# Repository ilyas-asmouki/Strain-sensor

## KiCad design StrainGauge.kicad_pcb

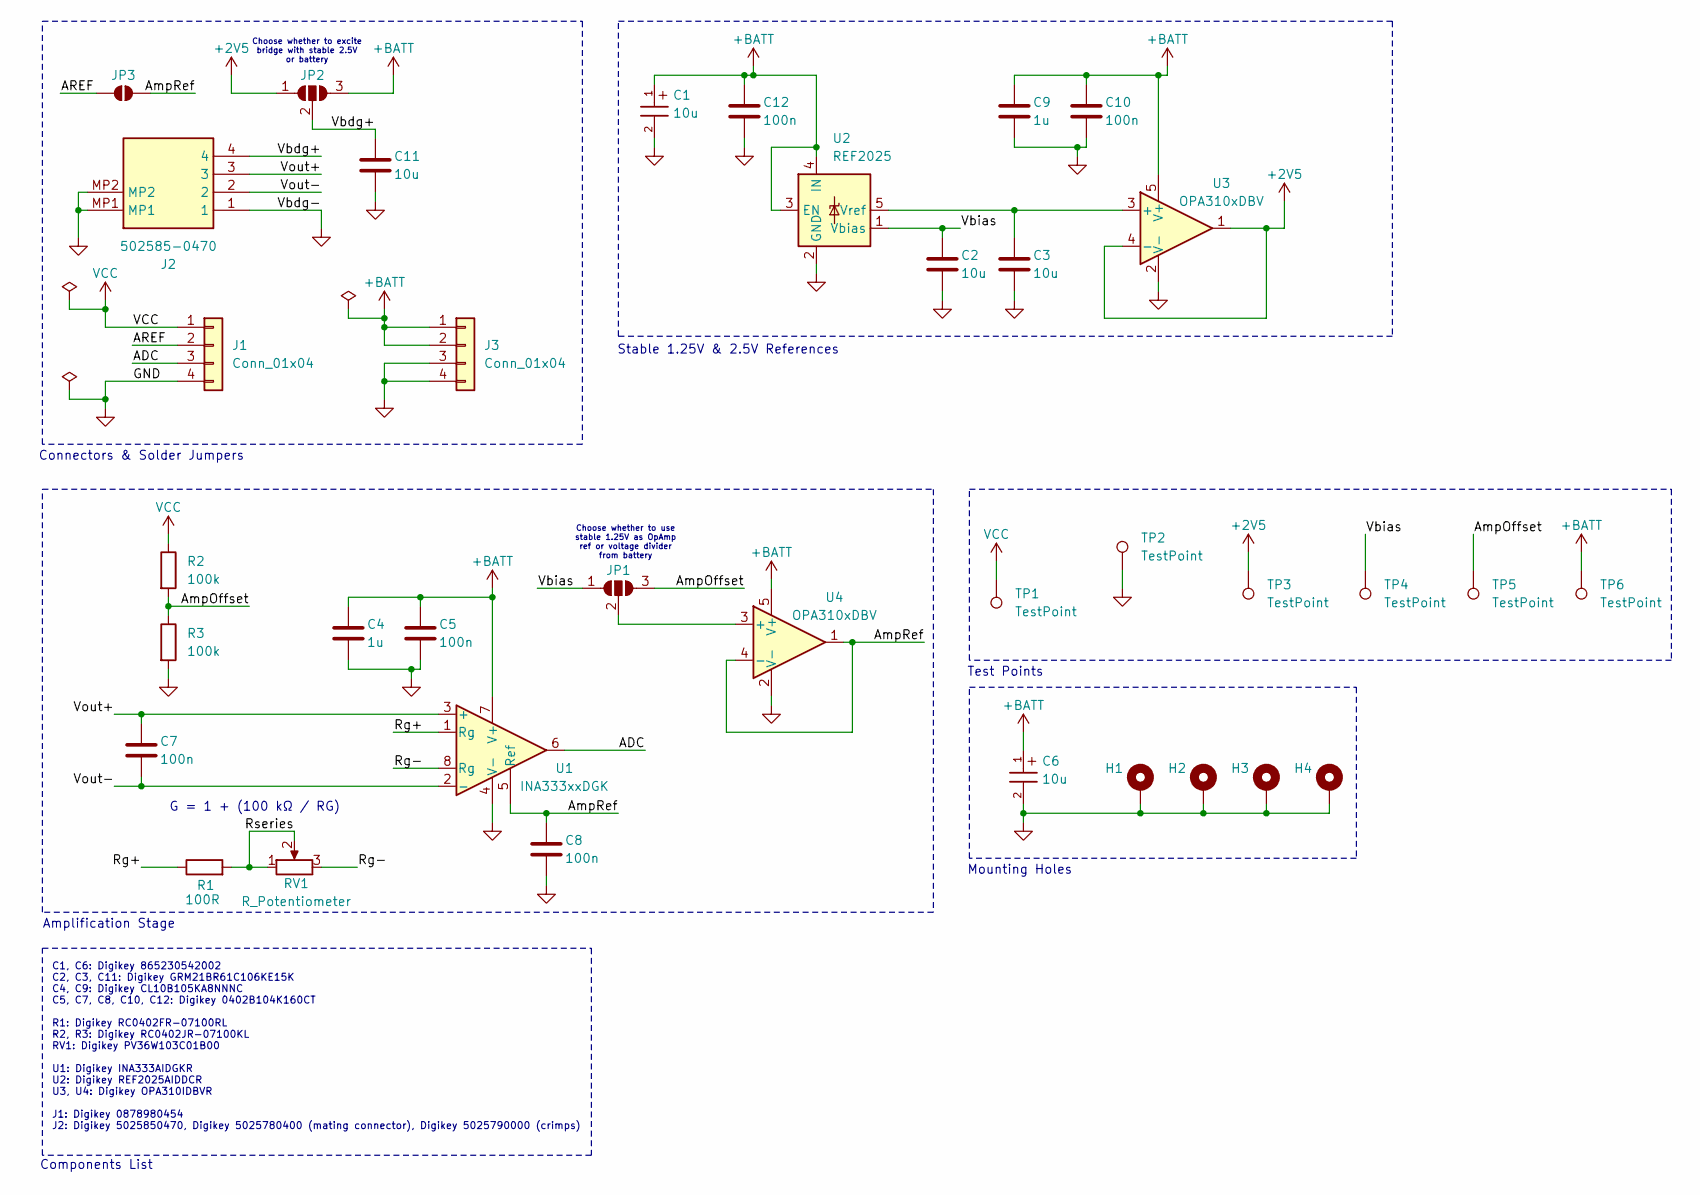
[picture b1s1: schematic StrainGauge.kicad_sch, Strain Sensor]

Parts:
C1, C6: 10u; WCAP-AS5H_5X5.5_DXL_
C2, C3, C11: 10u; C_0805_2012Metric
C4, C9: 1u; C_0603_1608Metric
C5, C7, C8, C10, C12: 100n; C_0402_1005Metric
H1, H2, H3, H4: MountingHole_Pad; MountingHole_2.2mm_M2_Pad_Via
J1: Conn_01x04; PinHeader_1x04_P2.54mm_Vertical
J2: 502585-0470; 5025850470; Mouser Part Number 538-502585-0470
J3: Conn_01x04; PinSocket_1x04_P2.54mm_Vertical
JP1, JP2: SolderJumper_3_Open; SolderJumper-3_P1.3mm_Open_RoundedPad1.0x1.5mm
JP3: SolderJumper_2_Open; SolderJumper-2_P1.3mm_Open_RoundedPad1.0x1.5mm
R1: 100R; R_0402_1005Metric
R2, R3: 100k; R_0402_1005Metric
RV1: R_Potentiometer; RES3_PV36W103C01B00_BRN
TP1, TP2, TP3, TP4, TP5, TP6: TestPoint; TestPoint_Pad_2.0x2.0mm
U1: INA333xxDGK; VSSOP-8_3x3mm_P0.65mm
U2: REF2025; SOT-23-5
U3, U4: OPA310xDBV; SOT-23-5

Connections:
+2V5: JP2.1 (A), TP3.1, U3.1, U3.4 (-)
+BATT: C1.1, C4.1, C5.1, C6.1, C9.1, C10.1, C12.1, J3.1, J3.2, JP2.3 (B), TP6.1, U1.7 (V+), U2.3 (EN), U2.4 (IN), U3.5 (V+), U4.5 (V+)
/ADC: J1.3, U1.6
/AREF: J1.2, JP3.1 (A)
/AmpOffset: JP1.3 (B), R2.2, R3.1, TP5.1
/AmpRef: C8.1, JP3.2 (B), U1.5 (Ref), U4.1, U4.4 (-)
/Rg+: R1.1, U1.1 (Rg)
/Rg-: RV1.3, U1.8 (Rg)
/Rseries: R1.2, RV1.1, RV1.2
/Vbdg+: C11.1, J2.4, JP2.2 (C)
/Vbias: C2.1, JP1.1 (A), TP4.1, U2.1 (Vbias)
/Vout+: C7.1, J2.3, U1.3 (+)
/Vout-: C7.2, J2.2, U1.2 (-)
GND: C1.2, C2.2, C3.2, C4.2, C5.2, C6.2, C8.2, C9.2, C10.2, C11.2, C12.2, H1.1, H2.1, H3.1, H4.1, J1.4, J2.1, J2.MP1, J2.MP2, J3.3, J3.4, R3.2, TP2.1, U1.4 (V-), U2.2 (GND), U3.2 (V-), U4.2 (V-)
unnamed: JP1.2 (C), U4.3 (+)
unnamed: C3.1, U2.5 (Vref), U3.3 (+)
VCC: J1.1, R2.1, TP1.1

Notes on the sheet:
Choose whether to excite bridge with stable 2.5V or battery
Choose whether to use stable 1.25V as OpAmp ref or voltage divider from battery
Test Points
Stable 1.25V & 2.5V References
C1, C6: Digikey 865230542002 C2, C3, C11: Digikey GRM21BR61C106KE15K C4, C9: Digikey CL10B105KA8NNNC C5, C7, C8, C10, C12: Digikey 0402B104K160CT R1: Digikey RC0402FR-07100RL R2, R3: Digikey RC0402JR-07100KL RV1: Digikey PV36W103C01B00 U1: Digikey INA333AIDGKR U2: Digikey REF2025AIDDCR U3, U4: Digi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
Mounting Holes
G = 1 + (100 kΩ / RG)
Connectors & Solder Jumpers
Amplification Stage
Components List

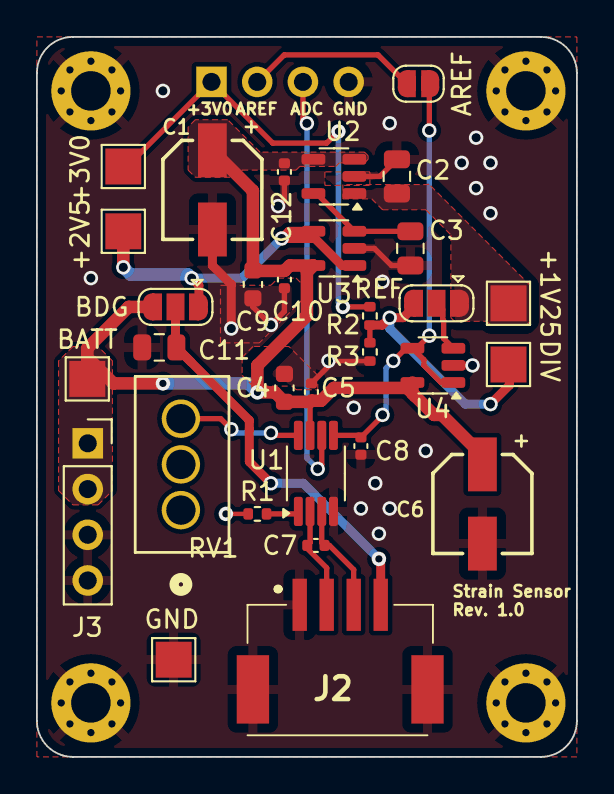
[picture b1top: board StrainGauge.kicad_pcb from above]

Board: 2 copper layers, 30.0 x 40.0 mm, 36 parts (1 on the bottom side), 17 nets.

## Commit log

2025-03-11 added limiting resistor + calculation
2025-03-11 removed garbage files
2025-03-12 added example schematic image of stable voltage source example
2025-03-12 added decoupling caps on input and power input of INA333
2025-03-12 added ref-voltage output buffer
2025-03-13 minor changes, need to add potentiometer next
2025-03-13 added potentiometer
2025-03-14 small fixes
2025-03-17 added footprints and 3D models
2025-03-25 added buffer on Ref pin of INA333 (very important), added components list and mostly cleanup
2025-03-26 first spice simulations, step models for components and first version of PCB
2025-03-27 fixed constraint violations
2025-03-27 added gerbers
2025-03-28 added power connector for external battery
2025-04-30 added production files
2025-05-19 added test note #1
2025-05-30 added test note #2
2025-05-31 added test note #3 + completed revision 1.0
